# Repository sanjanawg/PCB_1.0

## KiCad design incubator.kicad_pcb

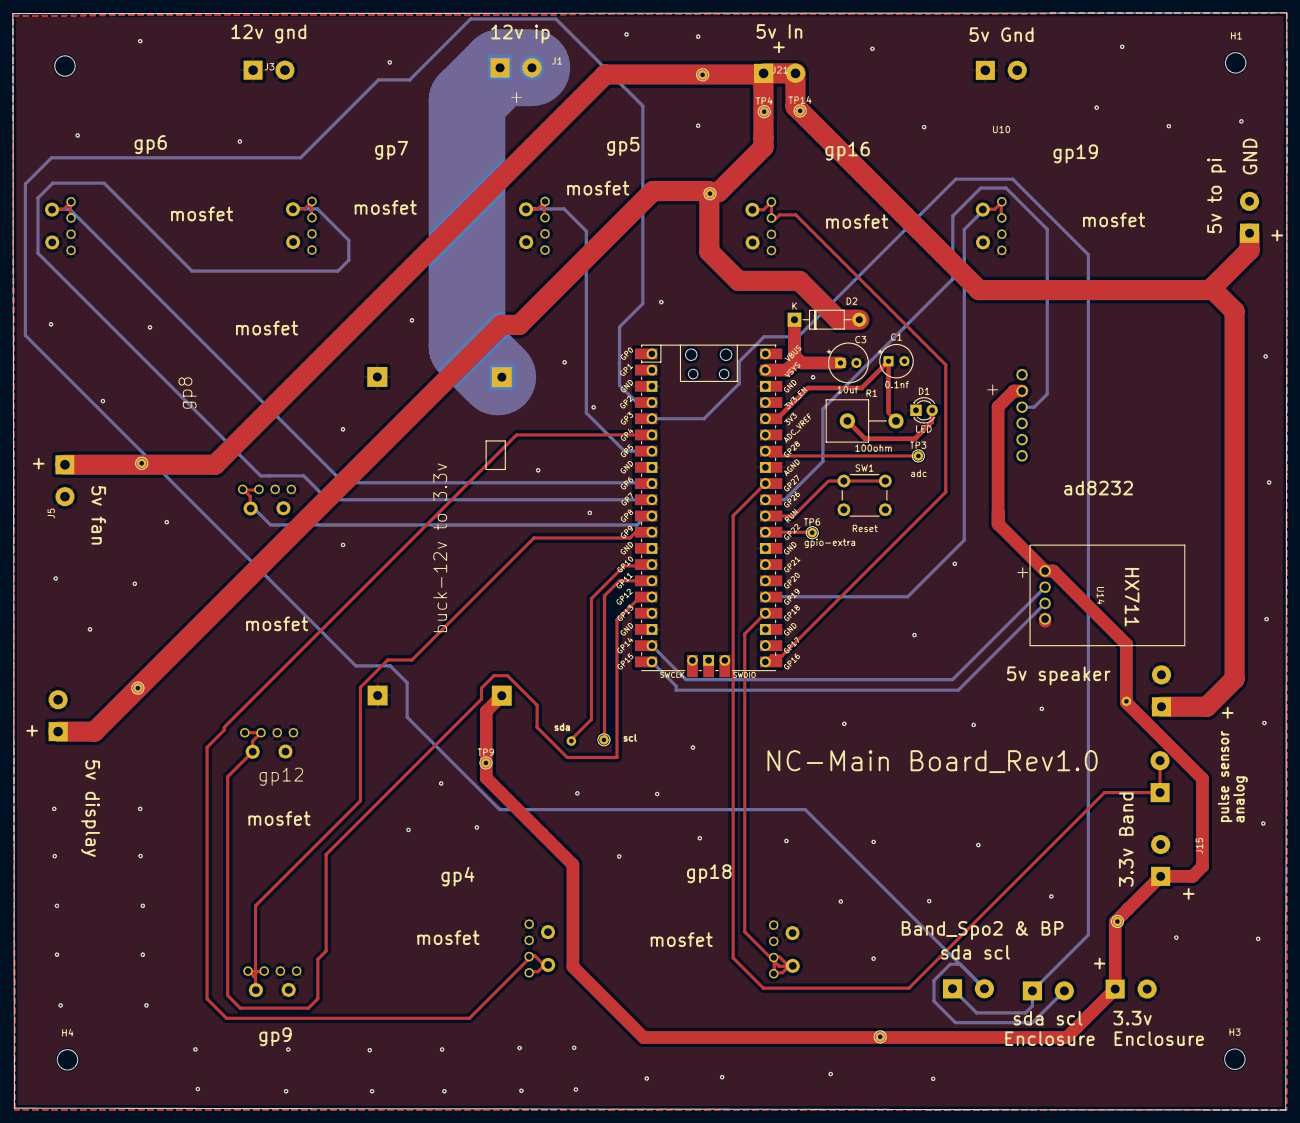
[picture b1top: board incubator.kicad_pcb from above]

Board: 2 copper layers, 199.7 x 171.9 mm, 49 parts (0 on the bottom side), 27 nets.

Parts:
C1: 0.1nf; CP_Radial_Tantal_D5.0mm_P2.50mm
C3: 10uf; CP_Radial_Tantal_D6.0mm_P2.50mm
D1: LED; LED_D3.0mm_FlatTop
D2: 1N5817; D_DO-41_SOD81_P10.16mm_Horizontal
H1, H2, H3, H4: MountingHole; MountingHole_3.2mm_M3
J1, J2, J3, J5, J6, J12, J13, J15, J16, J17, J20, J21, J22: Screw_Terminal_01x02; screw_terminal
R1: 100; R_Axial_Power_L20.0mm_W6.4mm_P7.62mm_Vertical
SW1: SW_Push; SW_PUSH_6mm_H5mm
TP3: adc; TestPoint_THTPad_D1.5mm_Drill0.7mm
TP4, TP5, TP7, TP8, TP9, TP10, TP11, TP13, TP14: sda; TestPoint_THTPad_D1.5mm_Drill0.7mm
TP6: gpio-extra; TestPoint_THTPad_D1.5mm_Drill0.7mm
U1, U4, U5, U6, U7, U8, U9, U11, U12, U13: switch
U2: buck_3.3
U3: Pico; RPi_Pico_SMD_TH
U10: ad8232
U14: hx711
scl: scl; TestPoint_THTPad_D1.5mm_Drill0.7mm

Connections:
3v3: J12.1, J16.1, TP9.1, TP10.1, TP11.1, U2.3 (out+), U10.2 (3v3), U14.1 (vcc)
5v: D2.2 (A), J2.1, J5.1, J6.1, J20.1, J21.1, J21.2, TP4.1, TP5.1, TP7.1, TP8.1, TP13.1, TP14.1
5v_mosfet: U1.1 (signal), U3.25 (GPIO19)
12v: J1.1, J1.2, U2.1 (in+)
12v_mosfet: U3.24 (GPIO18), U13.1 (signal)
GND: C1.2, C3.2, D1.1 (K), J2.2, J3.1, J3.2, J5.2, J6.2, J12.2, J16.2, J20.2, J22.1, J22.2, SW1.2, U1.2 (gnd), U2.2 (in-), U2.4 (out-), U3.3 (GND), U3.8 (GND), U3.13 (GND), U3.18 (GND), U3.23 (GND), U3.28 (GND), U3.33 (AGND), U3.38 (GND), U4.2 (gnd), U5.2 (gnd), U6.2 (gnd), U7.2 (gnd), U8.2 (gnd), U9.2 (gnd), U10.1 (gnd), U11.2 (gnd), U12.2 (gnd), U13.2 (gnd), U14.4 (gnd)
unnamed: D1.2 (A), R1.1
unnamed: C3.1, D2.1 (K), U3.39 (VSYS)
unnamed: J17.1, J17.2, U3.32 (GPIO27_ADC1)
unnamed: C1.1, R1.2, U3.36 (3V3)
unnamed: U3.6 (GPIO4), U4.1 (signal)
unnamed: U3.7 (GPIO5), U5.1 (signal)
unnamed: U3.9 (GPIO6), U7.1 (signal)
unnamed: U3.10 (GPIO7), U8.1 (signal)
unnamed: U3.11 (GPIO8), U9.1 (signal)
unnamed: U3.15 (GPIO11), scl.1
unnamed: U3.21 (GPIO16), U6.1 (signal)
unnamed: TP6.1, U3.29 (GPIO22)
unnamed: TP3.1, U3.34 (GPIO28_ADC2)
unnamed: SW1.1, U3.30 (RUN)
unnamed: U3.31 (GPIO26_ADC0), U10.3 (output)
unnamed: U3.16 (GPIO12), U11.1 (signal)
unnamed: U3.12 (GPIO9), U12.1 (signal)
dt: U3.20 (GPIO15), U14.3 (dt)
sck: U3.19 (GPIO14), U14.2 (sck)
scl: J13.1, J15.1, U3.5 (GPIO3)
sda: J13.2, J15.2, U3.4 (GPIO2)
